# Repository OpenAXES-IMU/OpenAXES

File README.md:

# OpenAXES

**Hardware design files and source code for an open-access wireless IMU** developed at the [Institute of Microelectronic Systems](https://www.ims.uni-hannover.de/) at the Leibniz University Hannover, Germany.

The OpenAXES IMU is open-source hardware licensed under the CERN-OHL-S-v2+. This means that you are allowed to modify, share, or sell the design, **if** you adhere to the respecitive licenses (see section [License](#license) or [LICENSE.txt](/LICENSE.txt) for details).

If you use the OpenAXES project (or parts of it) in scientific work, please see the [Citation](#citation) section below.

## Hardware

The hardware subdirectory contains the ECAD design files for the OpenAXES PCB and its fabrication outputs, and MCAD files for the housing, the programming adapter, and a calibration fixture.

More information about the hardware and how to fabricate it can be found in [the README in the hardware folder](/hardware/README.md)

## Firmware

The OpenAXES firmware is written in C and based on the CC2652 SDK from Texas Instruments.
It is based on TI-RTOS and can be compiled with [Code Composer Studio (CCS)](https://www.ti.com/tool/CCSTUDIO).

More information on how to compile and flash the firmware can be found in [the README in the firmware folder](/firmware/README.md)

## Citation

If you use the OpenAXES project (or parts of it) in scientific work,
please cite our upcoming paper (**submitted for peer review - not published yet**).

> Title: "OpenAXES: An Open-Source Wireless Inertial Measurement Unit"
>
> Authors: Fritz Webering, Nils Stanislawski, Joseph Winkler, Sarah Kleinjohann, Holger Blume
>
> Journal: [IEEE Sensors Letters](https://ieee-sensors.org/ieee-sensors-letters/)

The correct precise citation will be updated as soon as possible.

# License

Copyright 2023 Nils Stanislawski (nils.stanislawski@ims.uni-hannover.de) and Fritz Webering (fritz.webering@ims.uni-hannover.de)

This documentation describes Open Hardware and is licensed under the CERN-OHL-S-v2 or any later version.

You may redistribute and modify this documentation under the terms of the CERN OHL-S-v2 (https://ohwr.org/cern_ohl_s_v2.txt) or any later version. This documentation is distributed WITHOUT ANY EXPRESS OR IMPLIED WARRANTY, INCLUDING OF MERCHANTABILITY, SATISFACTORY QUALITY AND FITNESS FOR A PARTICULAR PURPOSE. Please see the CERN OHL v2-S for applicable conditions

Source Location: https://github.com/OpenAXES-IMU/OpenAXES

For detailed license information on individual files, please see the file [LICENSE.txt](/LICENSE.txt) in the root folder of this repository.

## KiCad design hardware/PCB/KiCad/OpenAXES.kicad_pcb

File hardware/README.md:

# Hardware

The **Hardware** subdirectory contains the ECAD design files for the OpenAXES PCB and its fabrication outputs, and MCAD files for the housing and calibration fixture.

This documentation describes Open Hardware and is licensed under the CERN-OHL-S v2 or any later version. See [License](#license) below for more information.

## PCB

This directory comprises the Altium Designer and KiCad EDA files. 
Altium Designer is a globally renowned PCB and electronic design software. 
KiCad, on the other hand, is a free open source software suite for EDA. 
The use of these two platforms ensures our project is accessible to a broad range of users.

The OpenAXES hardware platform was originally developed using Altium Designer.
To allow for the use of open source EDA software tools it has been ported to KiCad.
Known differences in the design files are only found in the silkscreen layers, so that there are no restrictions on the underlying functionality of the PCB.

### Getting Started

To work with the files contained in this directory, you will need to have the appropriate software installed on your local machine.

- For Altium files, download and install [Altium Designer](https://www.altium.com/)
- For KiCad files, download and install [KiCad EDA](https://www.kicad.org/)

Once you have installed the appropriate software, clone the repository and navigate to the respective subdirectories to access the project files.

### Fabrication outpus

Fabrication outputs are provided in the _PCB/Altium/Project Outputs for OpenAXES_ subdirectory.
Output files for both single PCB and a panel optimized for mass production are included.
 
### Deprecated components

- **BMI160**; pin-compatible replacement: BMI270

## Housing

The housing for the OpenAXES IMU can be found in the **hardware/case** subdirectory.
It was designed in FreeCAD 0.20 for 3D-printing with a 0.4 mm diameter FDM nozzle.
If the 3D printer is tunes correctly, the two halves of the case will snap together and provide a tight fit for the PCB.

There are cutouts for the USB port, the power switch, the analog pads on the bottom of the PCB, and for the JTAG adapter.
The two holes at the top can be plugged with short pieces of transparent 3D-printing filament (1.75 mm diameter).
These will act as light guides for the top LEDs next to the battery.

## Programming adapter

The programming adapter found in the **hardware/programming-adapter** directory comprises a 3D-printable fixture and a single-layer PCB with spring loaded pins.
These work together with the case, holding the IMU in place and contacting the six pads on the underside of the IMU PCB, for JTAG programming or debugging.

The adapter can be used with any JTAG adapter compatible with the CC2652 processor and the Code Composer Studio IDE.
During development, we used the LAUNCHXL-CC26X2R1 evaluation board from TI as a JTAG programmer.
All JTAG signals on that board are accessible on a pin header, which is normally populated with jumpers.
By removing the jumpers, the JTAG interface on the evaluation board can be used for external boards:

## Calibration fixture

The calibration fixture found in **hardware/calibrator** is an icosahedron (20-sided polyhedron) with a recess that accepts the IMU case.
This fixture can be used together the with scripts in the **calibration** directory to obtain the sensor calibration coefficients for each individual unit.

# License

Copyright 2023 Nils Stanislawski and Fritz Webering

This documentation describes Open Hardware and is licensed under the CERN-OHL-S-v2 or any later version.

You may redistribute and modify this documentation under the terms of the CERN OHL-S-v2 (https://ohwr.org/cern_ohl_s_v2.txt) or any later version. This documentation is distributed WITHOUT ANY EXPRESS OR IMPLIED WARRANTY, INCLUDING OF MERCHANTABILITY, SATISFACTORY QUALITY AND FITNESS FOR A PARTICULAR PURPOSE. Please see the CERN OHL v2-S for applicable conditions

Source Location: https://github.com/IMS-AS-LUH/OpenAXES

For detailed license information on individual files, please see the file [LICENSE.txt](/LICENSE.txt) in the root folder of this repository.

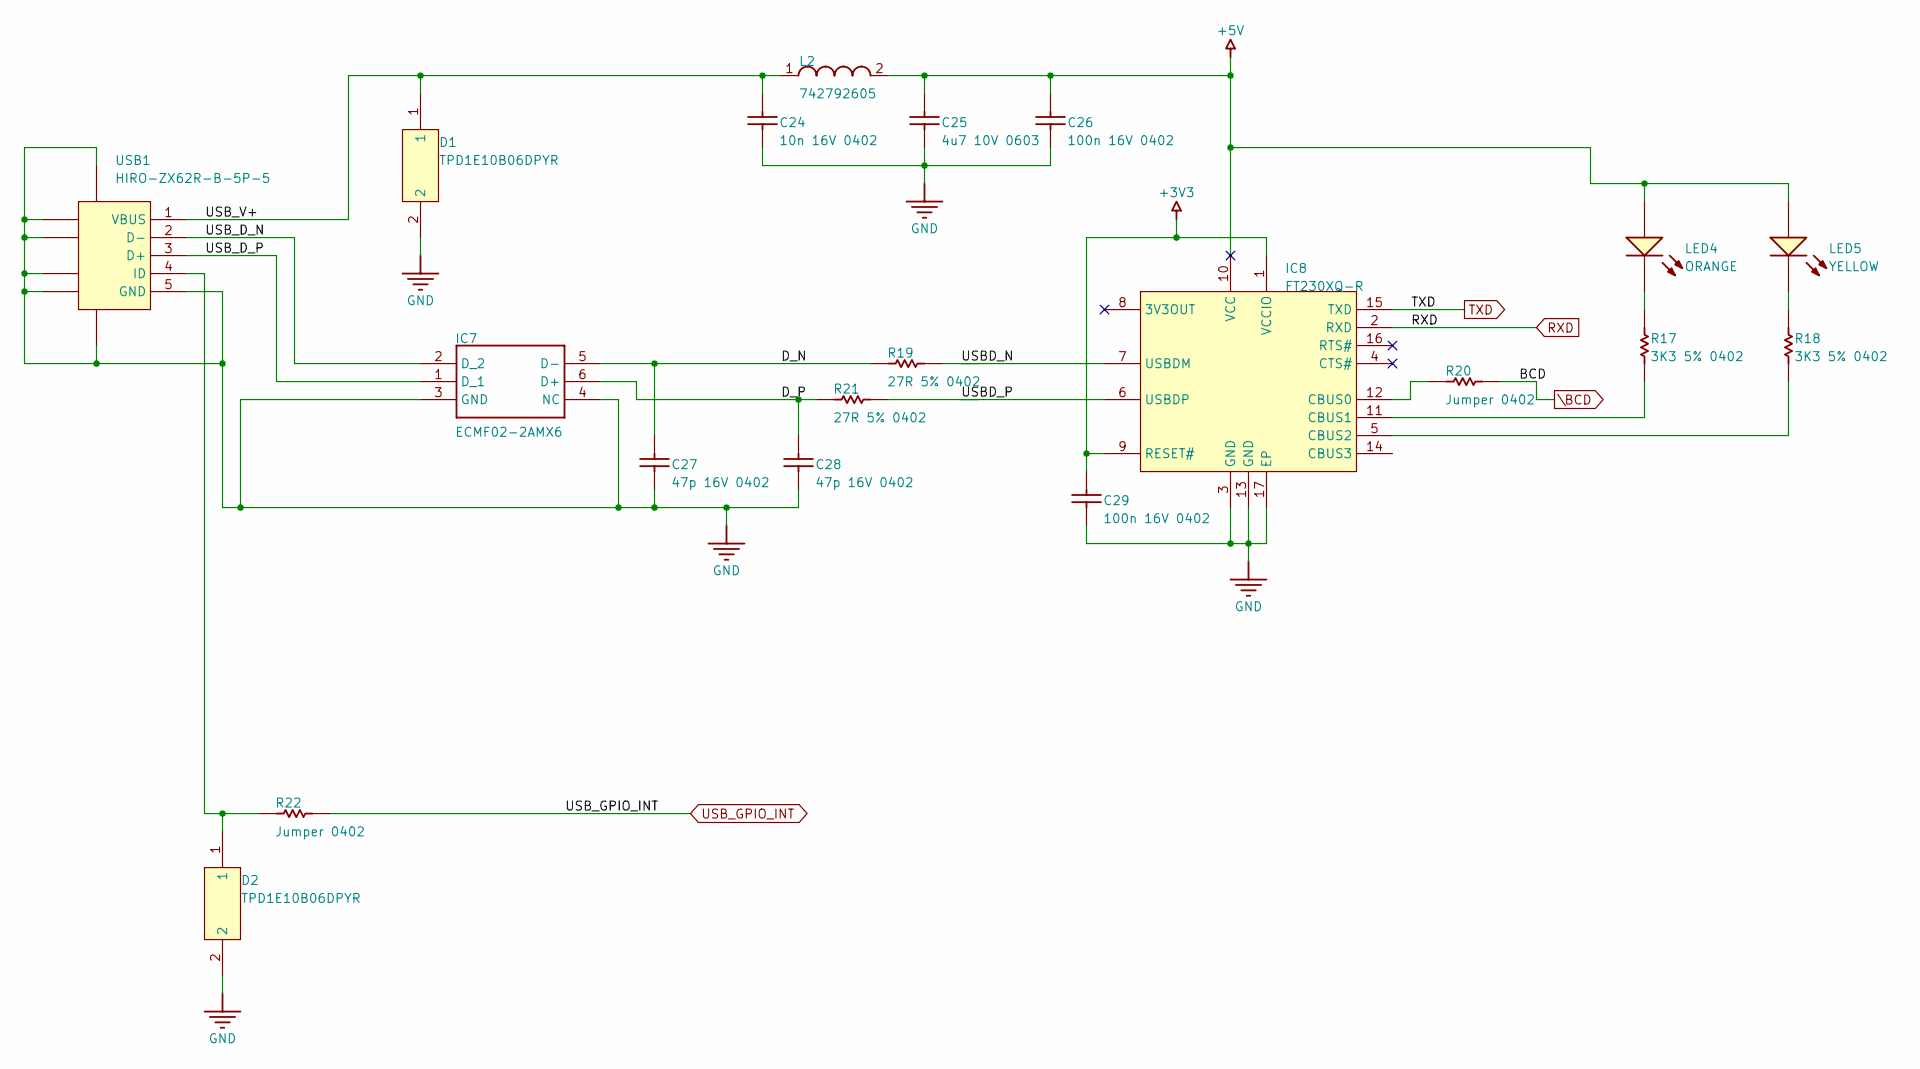
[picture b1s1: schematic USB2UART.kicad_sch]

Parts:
C24: 10n 16V 0402; CAPC0402(1005)33_L; TOLERANCE Â±10%; RATED VOLTAGE 16 V
C25: 4u7 10V 0603; CAPC0603(1608)100_L; TOLERANCE Â±20%; RATED VOLTAGE 10 V
C26: 100n 16V 0402; CAPC0402(1005)60_L; TOLERANCE Â±10%; RATED VOLTAGE 16 V
C27, C28: 47p 16V 0402; CAPC0402(1005)60_L; RATED VOLTAGE 16 V; TOLERANCE Â±10%
C29: 100n 16V 0402; CAPC0402(1005)60_N; TOLERANCE Â±10%; RATED VOLTAGE 16 V
D1, D2: TPD1E10B06DPYR; DPY0002A_M; BREAKDOWN VOLTAGE(MIN)(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 6; PARTNUMBER TPD1E10B06DPYR
IC7: ECMF02-2AMX6; SON50P150X170X55-6N-D; MANUFACTURER_PART_NUMBER ECMF02-2AMX6; MOUSER PART NUMBER 511-ECMF02-2AMX6
IC8: FT230XQ-R; QFN-16_L; PARTNUMBER FT230XQ-R
L2: 742792605; 0603(1608)_L
LED4: ORANGE; LED_0402
LED5: YELLOW; LED_0402
R17, R18: 3K3 5% 0402; RESC0402(1005)_L; TOLERANCE 5 %
R19, R21: 27R 5% 0402; RESC0402(1005)_L; TOLERANCE 5 %
R20, R22: Jumper 0402; RESC0402(1005)_L; TOLERANCE None
USB1: HIRO-ZX62R-B-5P-5; HIRO-ZX62R-B-5P_V

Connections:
+3V3: C29.2, IC8.1 (VCCIO), IC8.9 (RESET#); also elsewhere on the board
+5V: C25.2, C26.2, IC8.10 (VCC), L2.2, LED4.ANODE, LED5.ANODE; also elsewhere on the board
/USB2UART/D_N: C27.2, IC7.5 (D-), R19.1
/USB2UART/D_P: C28.2, IC7.6 (D+), R21.1
/USB2UART/USBD_N: IC8.7 (USBDM), R19.2
/USB2UART/USBD_P: IC8.6 (USBDP), R21.2
/USB2UART/USB_D_N: IC7.2 (D_2), USB1.2 (D-)
/USB2UART/USB_D_P: IC7.1 (D_1), USB1.3 (D+)
/USB2UART/USB_V+: C24.2, D1.1, L2.1, USB1.1 (VBUS)
GND: C24.1, C25.1, C26.1, C27.1, C28.1, C29.1, D1.2, D2.2, IC7.3 (GND), IC7.4 (NC), IC8.3 (GND), IC8.13 (GND), IC8.17 (EP), USB1.5 (GND), USB1.6 (SHLD), USB1.7 (SHLD), USB1.8 (SHLD), USB1.9 (SHLD), USB1.10 (SHLD), USB1.11 (SHLD); also elsewhere on the board
unnamed: IC8.12 (CBUS0), R20.1
unnamed: IC8.11 (CBUS1), R17.1
unnamed: IC8.5 (CBUS2), R18.1
unnamed: LED4.CATHODE, R17.2
unnamed: LED5.CATHODE, R18.2
unnamed: D2.1, R22.1, USB1.4 (ID)
RXD: IC8.2 (RXD); also elsewhere on the board
TXD: IC8.15 (TXD); also elsewhere on the board
USB_GPIO_INT: R22.2; also elsewhere on the board
\BCD: R20.2; also elsewhere on the board

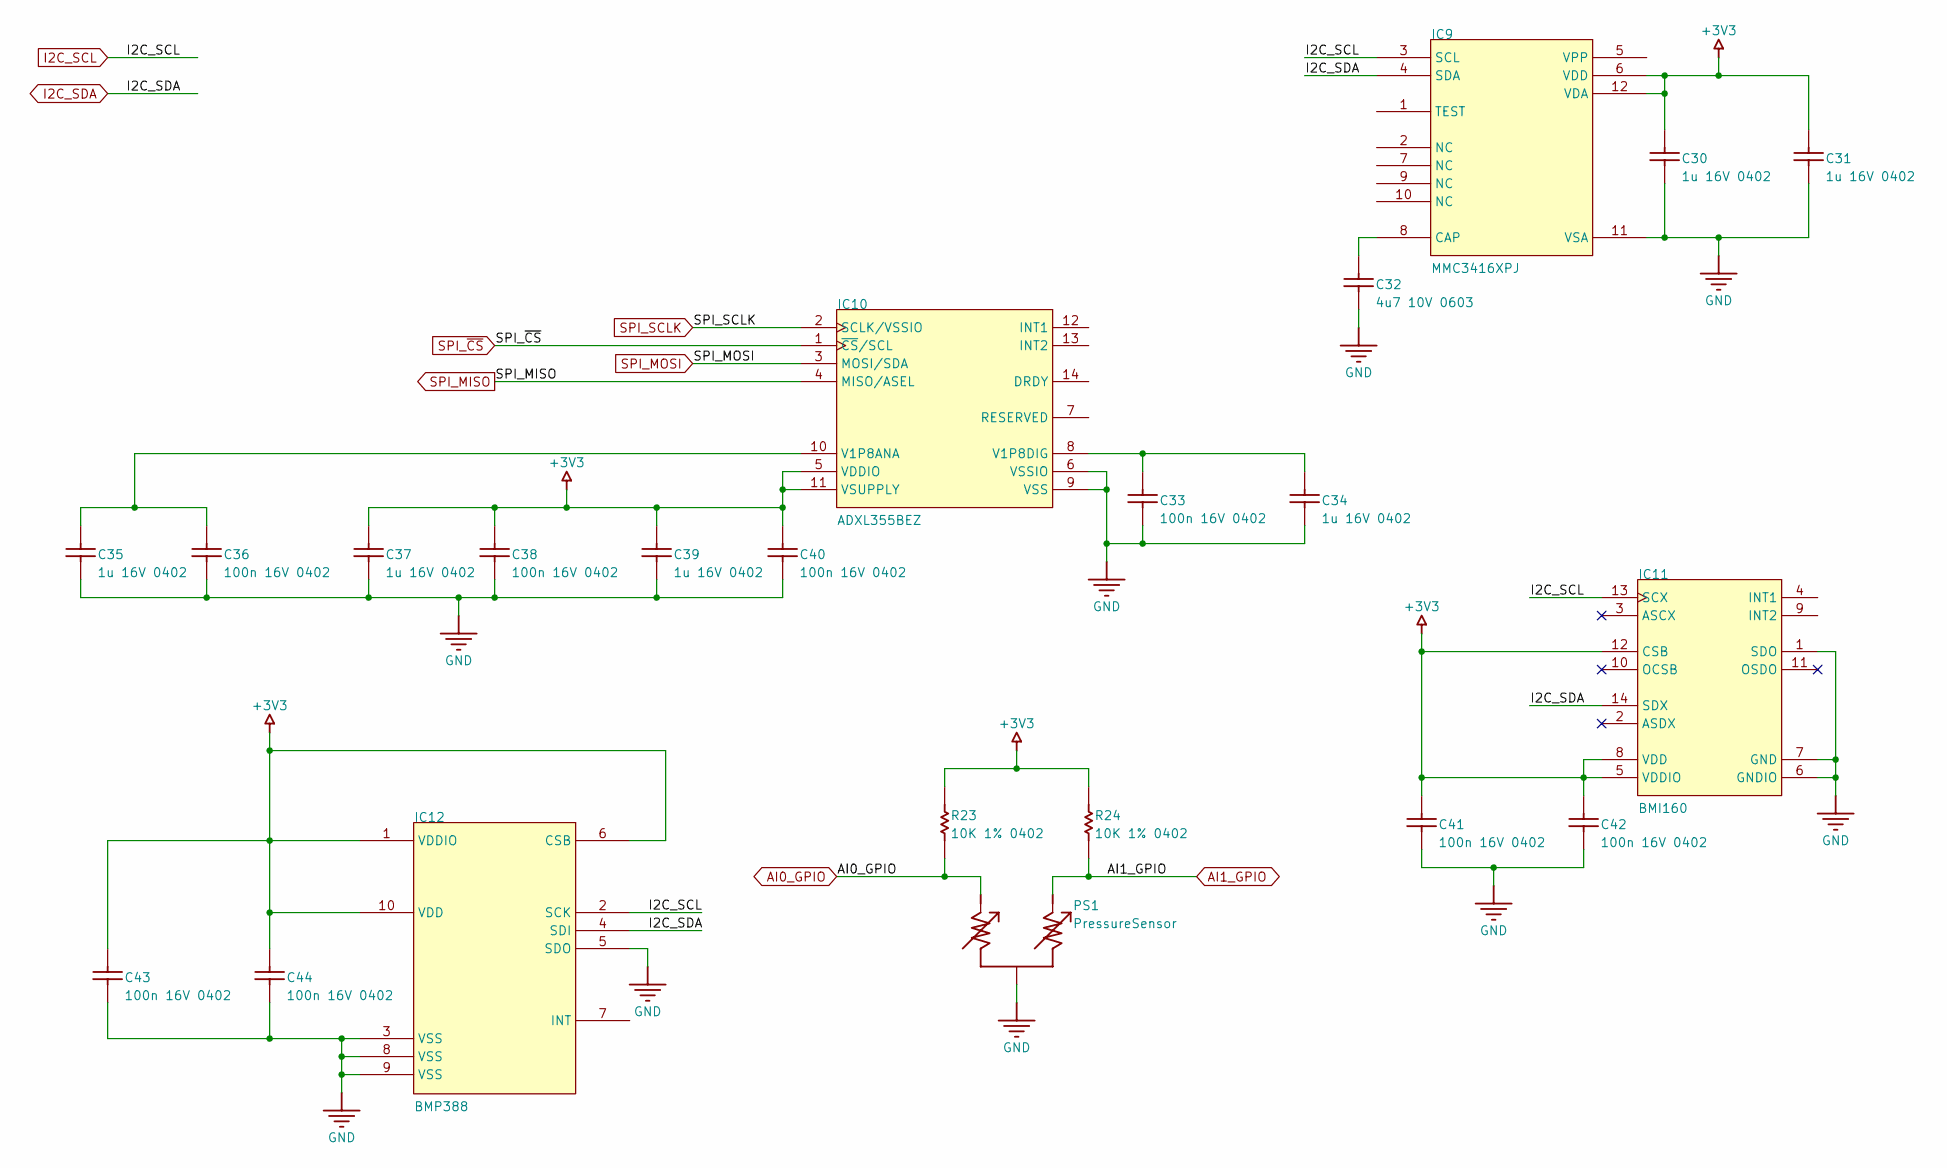
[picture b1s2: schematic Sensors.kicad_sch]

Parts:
C30, C31, C34, C35, C37, C39: 1u 16V 0402; CAPC0402(1005)60_L; RATED VOLTAGE 16 V; TOLERANCE Â±10%
C32: 4u7 10V 0603; CAPC0603(1608)100_L; TOLERANCE Â±20%; RATED VOLTAGE 10 V
C33, C36, C38, C40, C41, C42, C43, C44: 100n 16V 0402; CAPC0402(1005)60_L; TOLERANCE Â±10%; RATED VOLTAGE 16 V
IC9: MMC3416XPJ; BGA12C40P4X4_160X160X72
IC10: ADXL355BEZ; ADI-ADXL355-LCC-14_V
IC11: BMI160; BOSC-BMI160_V
IC12: BMP388
PS1: PressureSensor; PRESSURESENSOR
R23, R24: 10K 1% 0402; RESC0402(1005)_L; TOLERANCE 1 %

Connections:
+3V3: C30.1, C31.1, C37.1, C38.2, C39.1, C40.2, C41.2, C42.2, C43.2, C44.2, IC9.6 (VDD), IC9.12 (VDA), IC10.5 (VDDIO), IC10.11 (VSUPPLY), IC11.5 (VDDIO), IC11.8 (VDD), IC11.12 (CSB), IC12.1 (VDDIO), IC12.6 (CSB), IC12.10 (VDD), R23.2, R24.2; also elsewhere on the board
AI0_GPIO: PS1.3, R23.1; also elsewhere on the board
AI1_GPIO: PS1.2, R24.1; also elsewhere on the board
GND: C30.2, C31.2, C32.1, C33.1, C34.2, C35.2, C36.1, C37.2, C38.1, C39.2, C40.1, C41.1, C42.1, C43.1, C44.1, IC9.11 (VSA), IC10.6 (VSSIO), IC10.9 (VSS), IC11.1 (SDO), IC11.6 (GNDIO), IC11.7 (GND), IC12.3 (VSS), IC12.5 (SDO), IC12.8 (VSS), IC12.9 (VSS), PS1.1 (24); also elsewhere on the board
I2C_SCL: IC9.3 (SCL), IC11.13 (SCX), IC12.2 (SCK); also elsewhere on the board
I2C_SDA: IC9.4 (SDA), IC11.14 (SDX), IC12.4 (SDI); also elsewhere on the board
unnamed: C32.2, IC9.8 (CAP)
unnamed: C35.1, C36.2, IC10.10 (V1P8ANA)
unnamed: C33.2, C34.1, IC10.8 (V1P8DIG)
SPI_MISO: IC10.4 (MISO/ASEL); also elsewhere on the board
SPI_MOSI: IC10.3 (MOSI/SDA); also elsewhere on the board
SPI_SCLK: IC10.2 (SCLK/VSSIO); also elsewhere on the board
SPI_~CS: IC10.1 (~CS/SCL); also elsewhere on the board

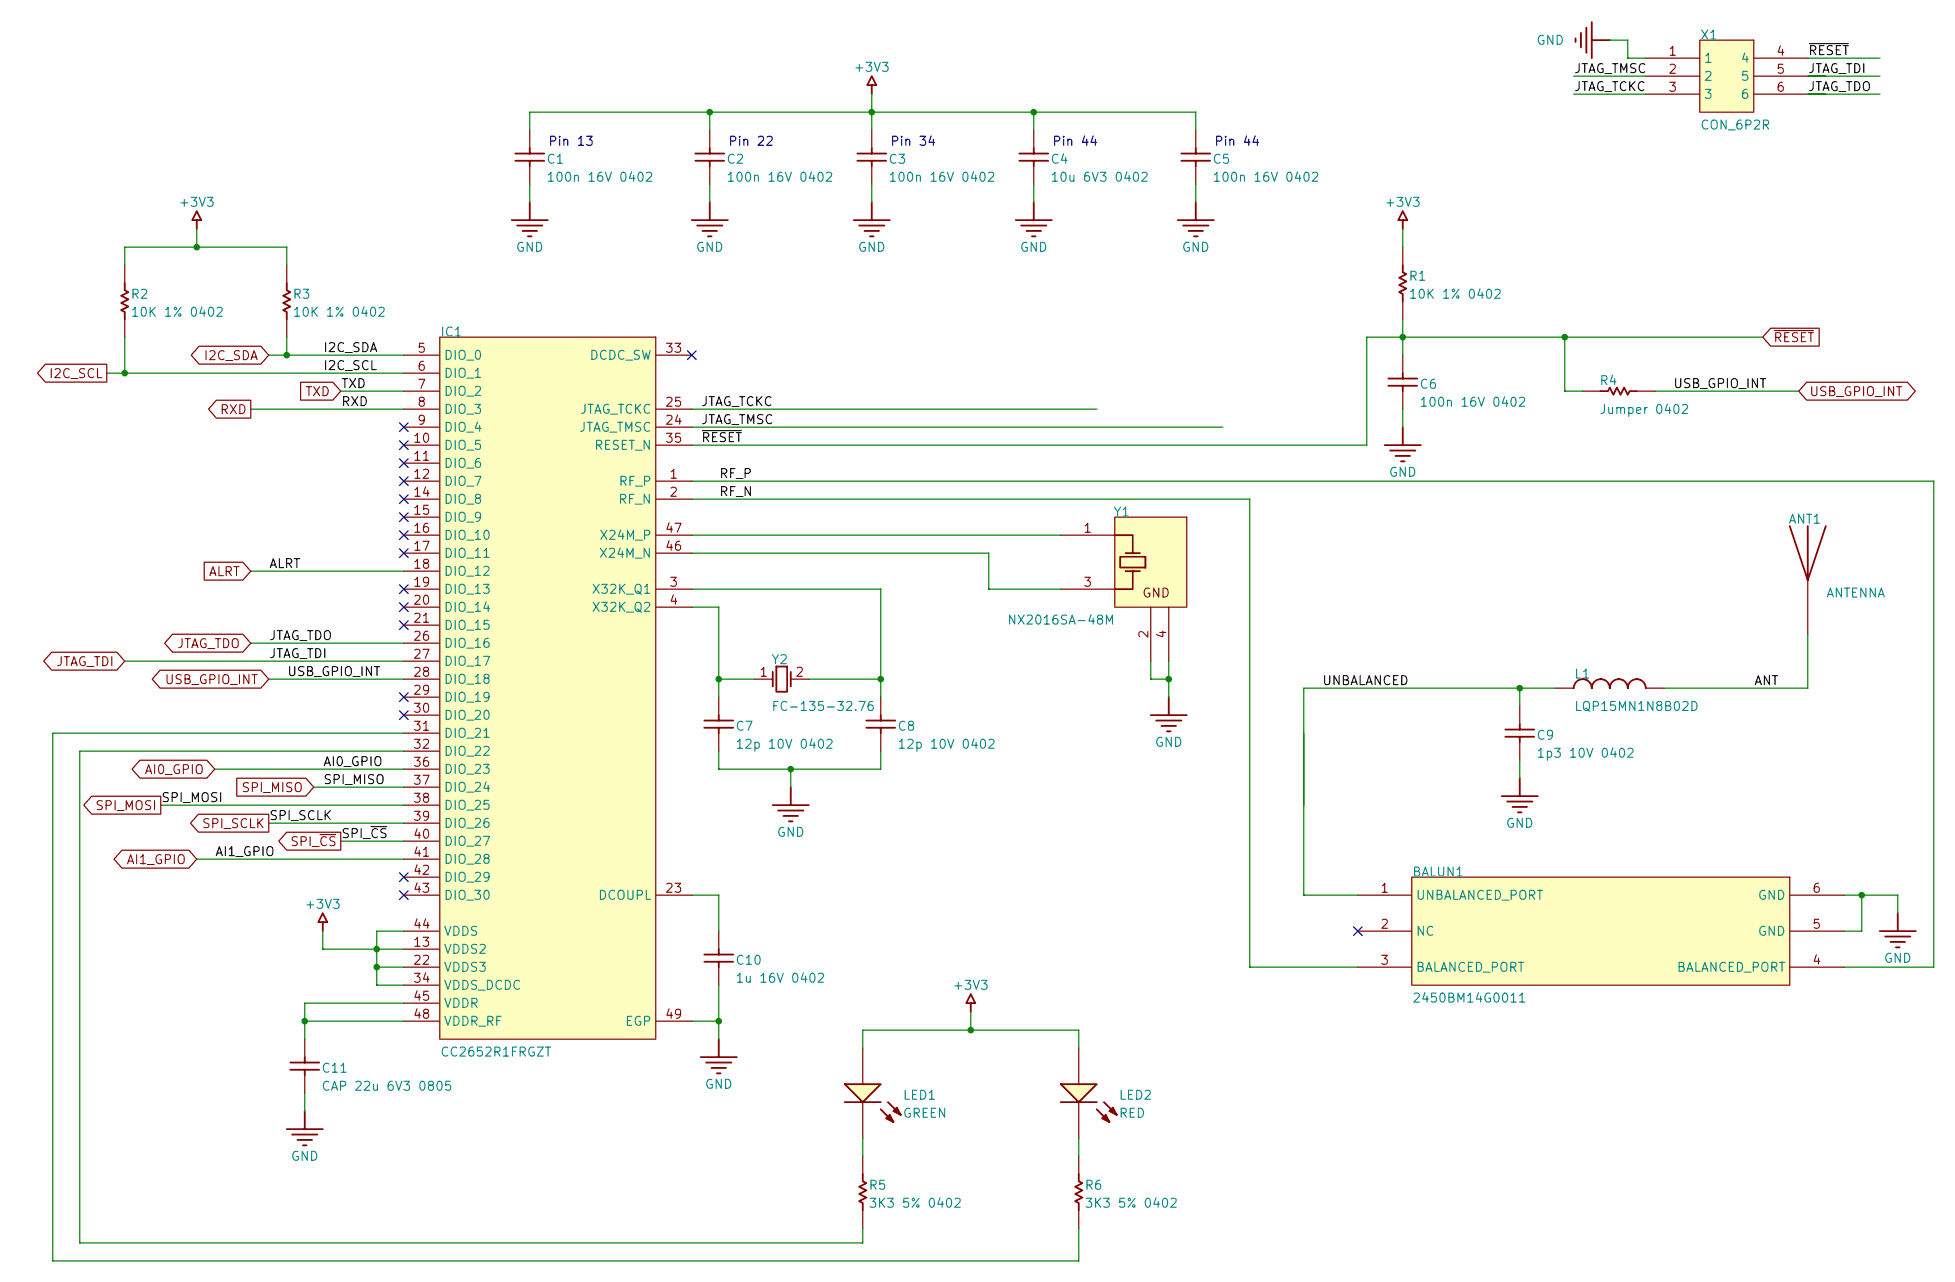
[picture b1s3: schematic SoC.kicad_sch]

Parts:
ANT1: ANTENNA; MOLEX_47948-0001
BALUN1: 2450BM14G0011; SON50P80X70-6L
C1, C2, C3, C5, C6: 100n 16V 0402; CAPC0402(1005)60_L; TOLERANCE Â±10%; RATED VOLTAGE 16 V
C4: 10u 6V3 0402; CAPC0402(1005)60_L; TOLERANCE Â±20%; RATED VOLTAGE 6.3 V
C7, C8: 12p 10V 0402; CAPC0402(1005)60_L; TOLERANCE Â±1%; RATED VOLTAGE 10 V
C9: 1p3 10V 0402; CAPC0402(1005)60_M; RATED VOLTAGE 10 V; TOLERANCE Â±0.25pF
C10: 1u 16V 0402; CAPC0402(1005)60_N; RATED VOLTAGE 16 V; TOLERANCE Â±10%
C11: CAP 22u 6V3 0805; CAPC0805(2012)145_L; RATED VOLTAGE 6.3 V; TOLERANCE Â±10%
IC1: CC2652R1FRGZT; RGZ0048A_V
L1: LQP15MN1N8B02D; INDC1005X45X25ML10T10; TOLERANCE (NH) ±0.1nH
LED1: GREEN; LED_0402
LED2: RED; LED_0402
R1, R2, R3: 10K 1% 0402; RESC0402(1005)_L; TOLERANCE 1 %
R4: Jumper 0402; RESC0402(1005)_L; TOLERANCE None
R5, R6: 3K3 5% 0402; RESC0402(1005)_L; TOLERANCE 5 %
X1: CON_6P2R; JTAG_CON
Y1: NX2016SA-48M; Crystal_2016
Y2: FC-135-32.76; EPSON-FC-135_V

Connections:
+3V3: C1.2, C2.2, C3.2, C4.2, C5.2, IC1.13 (VDDS2), IC1.22 (VDDS3), IC1.34 (VDDS_DCDC), IC1.44 (VDDS), LED1.ANODE, LED2.ANODE, R1.2, R2.2, R3.2; also elsewhere on the board
/SoC/ANT: ANT1.ANTENNA (23), L1.2
/SoC/JTAG_TCKC: IC1.25 (JTAG_TCKC), X1.3
/SoC/JTAG_TMSC: IC1.24 (JTAG_TMSC), X1.2
/SoC/RF_N: BALUN1.3 (BALANCED_PORT), IC1.2 (RF_N)
/SoC/RF_P: BALUN1.4 (BALANCED_PORT), IC1.1 (RF_P)
/SoC/UNBALANCED: BALUN1.1 (UNBALANCED_PORT), C9.2, L1.1
AI0_GPIO: IC1.36 (DIO_23); also elsewhere on the board
AI1_GPIO: IC1.41 (DIO_28); also elsewhere on the board
ALRT: IC1.18 (DIO_12); also elsewhere on the board
GND: BALUN1.5 (GND), BALUN1.6 (GND), C1.1, C2.1, C3.1, C4.1, C5.1, C6.1, C7.1, C8.1, C9.1, C10.1, C11.1, IC1.49 (EGP), X1.1, Y1.2 (GND), Y1.4 (GND); also elsewhere on the board
I2C_SCL: IC1.6 (DIO_1), R2.1; also elsewhere on the board
I2C_SDA: IC1.5 (DIO_0), R3.1; also elsewhere on the board
JTAG_TDI: IC1.27 (DIO_17), X1.5
JTAG_TDO: IC1.26 (DIO_16), X1.6
unnamed: C10.2, IC1.23 (DCOUPL)
unnamed: IC1.31 (DIO_21), R6.1
unnamed: IC1.32 (DIO_22), R5.1
unnamed: C11.2, IC1.45 (VDDR), IC1.48 (VDDR_RF)
unnamed: IC1.46 (X24M_N), Y1.3 (X2)
unnamed: IC1.47 (X24M_P), Y1.1 (X1)
unnamed: C8.2, IC1.3 (X32K_Q1), Y2.2
unnamed: C7.2, IC1.4 (X32K_Q2), Y2.1
unnamed: LED1.CATHODE, R5.2
unnamed: LED2.CATHODE, R6.2
RXD: IC1.8 (DIO_3); also elsewhere on the board
SPI_MISO: IC1.37 (DIO_24); also elsewhere on the board
SPI_MOSI: IC1.38 (DIO_25); also elsewhere on the board
SPI_SCLK: IC1.39 (DIO_26); also elsewhere on the board
SPI_~CS: IC1.40 (DIO_27); also elsewhere on the board
TXD: IC1.7 (DIO_2); also elsewhere on the board
USB_GPIO_INT: IC1.28 (DIO_18), R4.2; also elsewhere on the board
~RESET: C6.2, IC1.35 (RESET_N), R1.1, R4.1, X1.4

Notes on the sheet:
Pin 44
Pin 34
Pin 13
Pin 22

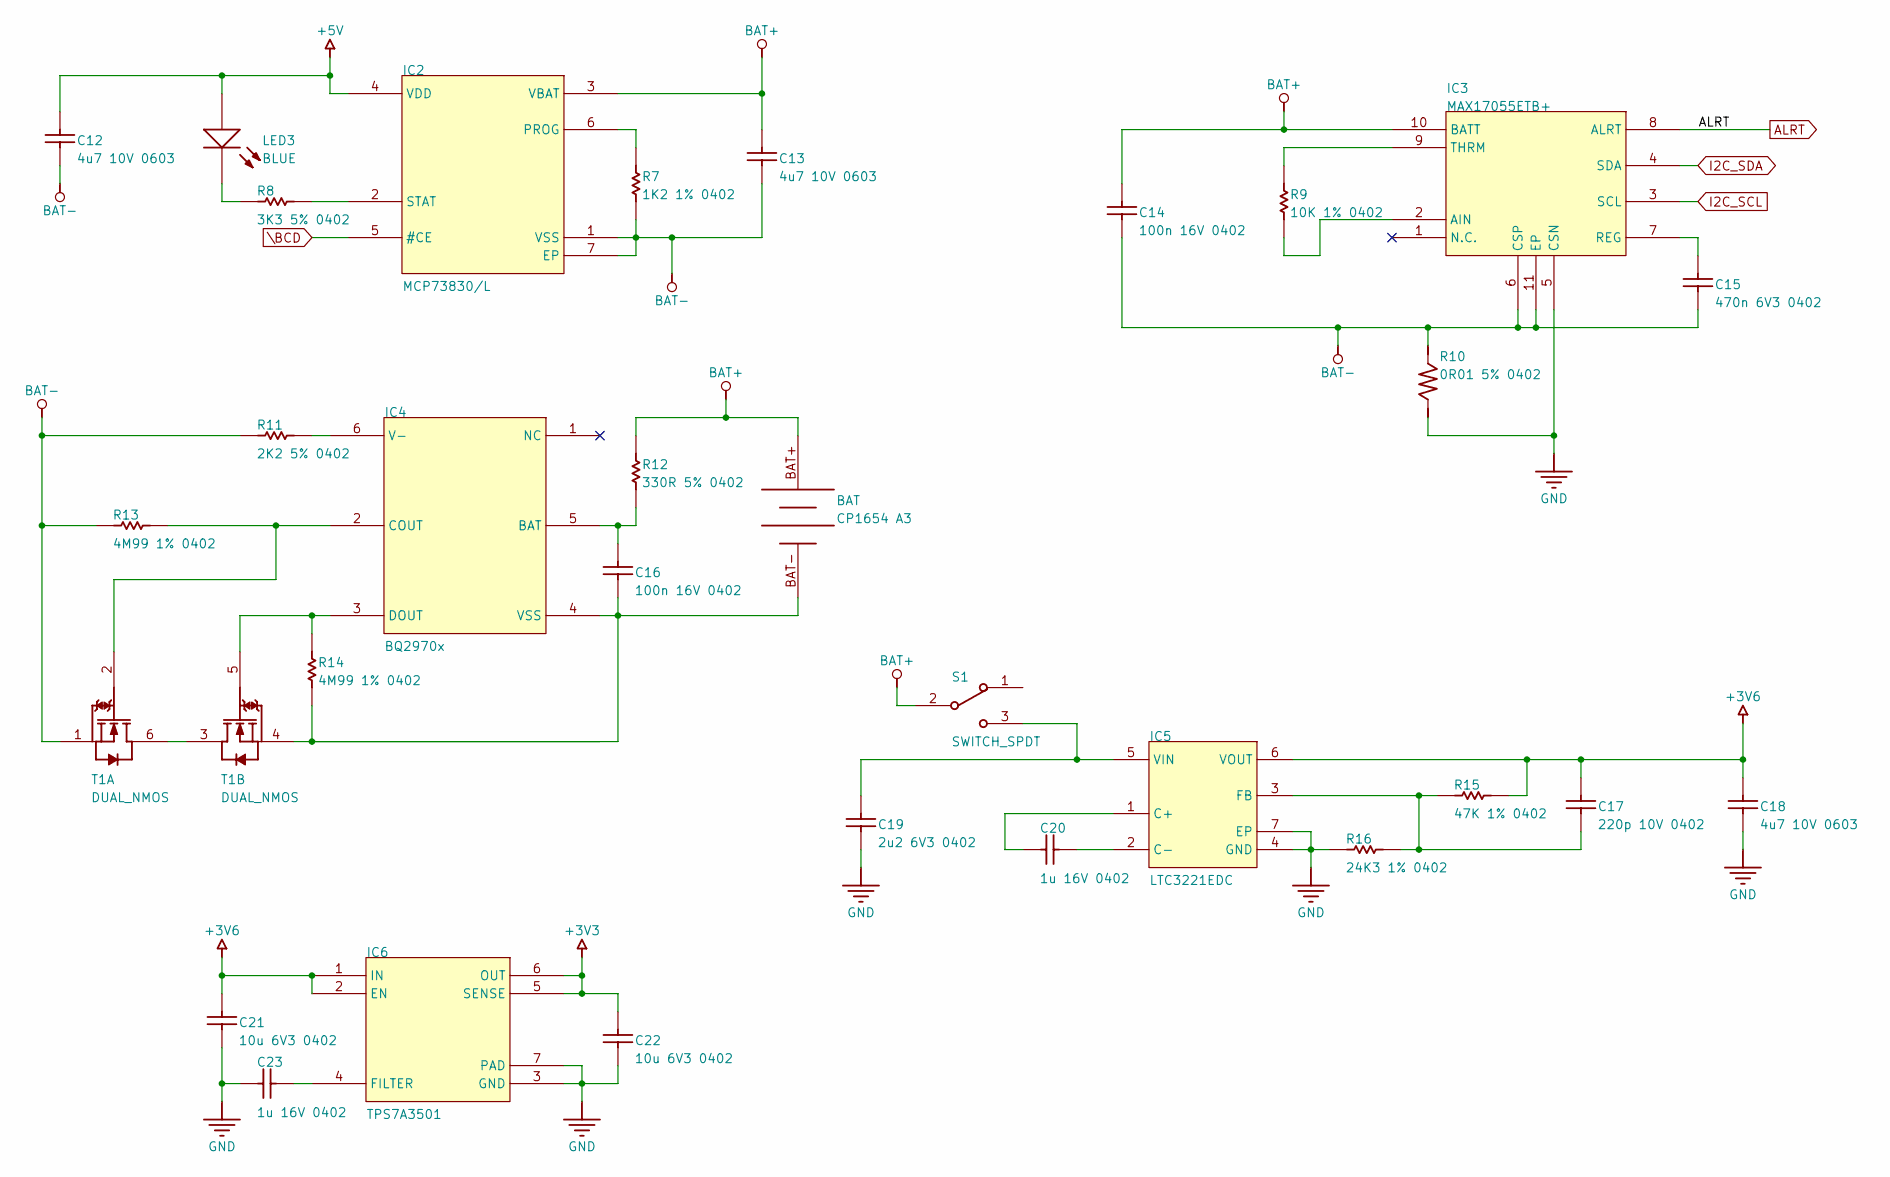
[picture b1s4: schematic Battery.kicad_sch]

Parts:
BAT: CP1654 A3; CP1654
C12, C13, C18: 4u7 10V 0603; CAPC0603(1608)100_L; TOLERANCE Â±20%; RATED VOLTAGE 10 V
C14, C16: 100n 16V 0402; CAPC0402(1005)60_L; TOLERANCE Â±10%; RATED VOLTAGE 16 V
C15: 470n 6V3 0402; CAPC0402(1005)60_L; RATED VOLTAGE 6.3 V; TOLERANCE Â±10%
C17: 220p 10V 0402; CAPC0402(1005)60_L; RATED VOLTAGE 10 V; TOLERANCE Â±5%
C19: 2u2 6V3 0402; CAPC0402(1005)60_L; RATED VOLTAGE 6.3 V; TOLERANCE Â±10%
C20, C23: 1u 16V 0402; CAPC0402(1005)60_L; RATED VOLTAGE 16 V; TOLERANCE Â±10%
C21, C22: 10u 6V3 0402; CAPC0402(1005)60_L; TOLERANCE Â±20%; RATED VOLTAGE 6.3 V
IC2: MCP73830/L; PSON50P200X80_HS-7L
IC3: MAX17055ETB+; PSON40P250X80_HS-11L
IC4: BQ2970x; SON50P150X80-6L
IC5: LTC3221EDC; LT-DC6-6_V; PARTNUMBER LTC3221EDC
IC6: TPS7A3501; PSON65P200X80_HS-7L
LED3: BLUE; LED_0402
R7: 1K2 1% 0402; RESC0402(1005)_L; TOLERANCE 1 %
R8: 3K3 5% 0402; RESC0402(1005)_L; TOLERANCE 5 %
R9: 10K 1% 0402; RESC0402(1005)_L; TOLERANCE 1 %
R10: 0R01 5% 0402; R0402
R11: 2K2 5% 0402; RESC0402(1005)_L; TOLERANCE 5 %
R12: 330R 5% 0402; RESC0402(1005)_L; TOLERANCE 5 %
R13, R14: 4M99 1% 0402; RESC0402(1005)_L; TOLERANCE 1 %
R15: 47K 1% 0402; RESC0402(1005)_L; TOLERANCE 1 %
R16: 24K3 1% 0402; RESC0402(1005)_L; TOLERANCE 1 %
S1: SWITCH_SPDT; SSSS810701_MODIFIED
T1: DUAL_NMOS; WDFN6 2X2 0.65P

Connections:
+3V3: C22.2, IC6.5 (SENSE), IC6.6 (OUT); also elsewhere on the board
+3V6: C17.2, C18.2, C21.2, IC5.6 (VOUT), IC6.1 (IN), IC6.2 (EN), R15.2
+5V: C12.2, IC2.4 (VDD), LED3.ANODE; also elsewhere on the board
ALRT: IC3.8 (ALRT); also elsewhere on the board
BAT+: C13.2, C14.2, IC2.3 (VBAT), IC3.10 (BATT), R12.2, S1.2; also elsewhere on the board
BAT-: C12.1, C13.1, C14.1, C15.1, IC2.1 (VSS), IC2.7 (EP), IC3.6 (CSP), IC3.11 (EP), R7.1, R10.1 (24), R11.1, R13.1, T1.1 (S1)
GND: C18.1, C19.1, C21.1, C22.1, C23.2, IC3.5 (CSN), IC5.4 (GND), IC5.7 (EP), IC6.3 (GND), IC6.7 (PAD), R10.2, R16.1; also elsewhere on the board
I2C_SCL: IC3.3 (SCL); also elsewhere on the board
I2C_SDA: IC3.4 (SDA); also elsewhere on the board
unnamed: IC2.6 (PROG), R7.2
unnamed: IC2.2 (STAT), R8.2
unnamed: IC3.2 (AIN), R9.1
unnamed: C15.2, IC3.7 (REG)
unnamed: IC3.9 (THRM), R9.2
unnamed: C16.2, IC4.5 (BAT), R12.1
unnamed: IC4.2 (COUT), R13.2, T1.2 (G1)
unnamed: IC4.3 (DOUT), R14.2, T1.5 (G2)
unnamed: IC4.6 (V-), R11.2
unnamed 43: C16.1, IC4.4 (VSS), R14.1, T1.4 (S2); also elsewhere on the board
unnamed: C20.2, IC5.1 (C+)
unnamed: C20.1, IC5.2 (C-)
unnamed: C17.1, IC5.3 (FB), R15.1, R16.2
unnamed: C19.2, IC5.5 (VIN), S1.3
unnamed: C23.1, IC6.4 (FILTER)
unnamed: LED3.CATHODE, R8.1
unnamed: T1.3 (D2), T1.6 (D1)
\BCD: IC2.5 (#CE); also elsewhere on the board

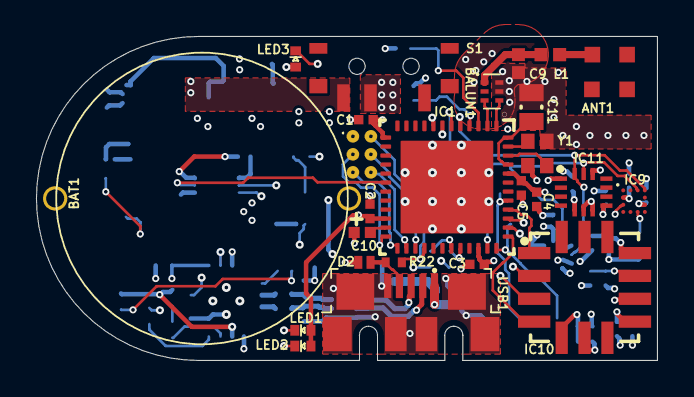
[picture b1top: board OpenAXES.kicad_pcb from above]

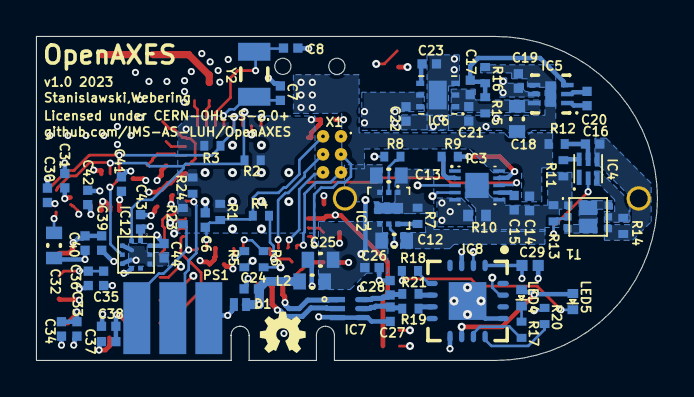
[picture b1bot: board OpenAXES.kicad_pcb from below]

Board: 4 copper layers, 34.5 x 18.0 mm, 99 parts (74 on the bottom side), 71 nets.

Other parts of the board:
BAT1: CP1654 A3; CP1654

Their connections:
BAT+: BAT1.BAT+; also elsewhere on the board
unnamed 43: BAT1.BAT-; also elsewhere on the board

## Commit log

2023-07-03 Added license, changes, and contributing files
2023-07-03 Added Altium source and output files for v1.0
2023-07-03 Added KiCad source files for v1.0
2023-07-03 Add Firmware
2023-07-03 Added graphical abstract to root README.md
2023-07-03 Started on hardware readme
2023-07-03 Update README with more information
2023-07-04 Add example dataset
2023-07-04 Add license information for README files
2023-07-04 Add 3D models for case, programmer and calibration fixture
2023-07-05 Add license and copyright info to documentation
2023-07-05 Add imu_control.py and README to tools
2023-07-05 hardware: Add/improve programmer images in README
2023-07-14 Add imu_tk_matlab as a submodule
2023-07-14 Add calibration scripts and documentation
2023-07-19 Update README.md
    Fixed link to source files
2023-07-20 Move imu_control scripts to /tools/imu_control/
2023-07-20 Fix wrong info in dataset README
2023-07-20 Fixed link to source files in calibration README
2023-08-22 calibration: Improve documentation
2023-08-23 tools: Add IMU quaternion visualization tool (Qt)

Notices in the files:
hardware/PCB/KiCad/OpenAXES.kicad_pcb:
Licensed under CERN-OHL-S-2.0+
